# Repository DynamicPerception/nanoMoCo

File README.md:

nanoMoCo Stepper Controller/Driver
==================================

The nanoMoCo stepper driver/controller is a specialized, Arduino-compatible* device specifically designed to enable advanced multi-axis stepper-based robotics and automation projects less expensive, and easier to create.

This github contains the Eagle files, BOM, and Sketchup files for this board.  To purchase a pre-made board, see http://dynamicperception.com/products/nanomoco-stepper-drivercontroller

Key features of the nanoMoCo include:

- Atmega328P processor running at 16MHz
- 8-16V DC Operation
- Integrated A4983/A4988 bi-polar chopping driver with up to 16x microstepping
     - Up to 800 mA/coil without active cooling
     - Up to 1.5 A/coil with active cooling
- Dual opto-coupled outputs for safe interaction with other devices
- Integrated RS485 bus for multi-node communication over long distances with only two wires
- Leverage the OpenMoCo AVR Libraries and OpenMoCo Qt Libraries to create new software and applications

* requires a special USB to RS485 adapter to use with the Arduino IDE

See http://dynamicperception.com/docs/nanomoco for more information

License and Copyright
---------------------

nanoMoCo is Copyright (c) 2012-2013 Dynamic Perception LLC.

All files shared under the Creative Commons Attibution-Share-Alike 3.0 License.

The nanoMoCo name is a trademark of Dynamic Perception LLC.

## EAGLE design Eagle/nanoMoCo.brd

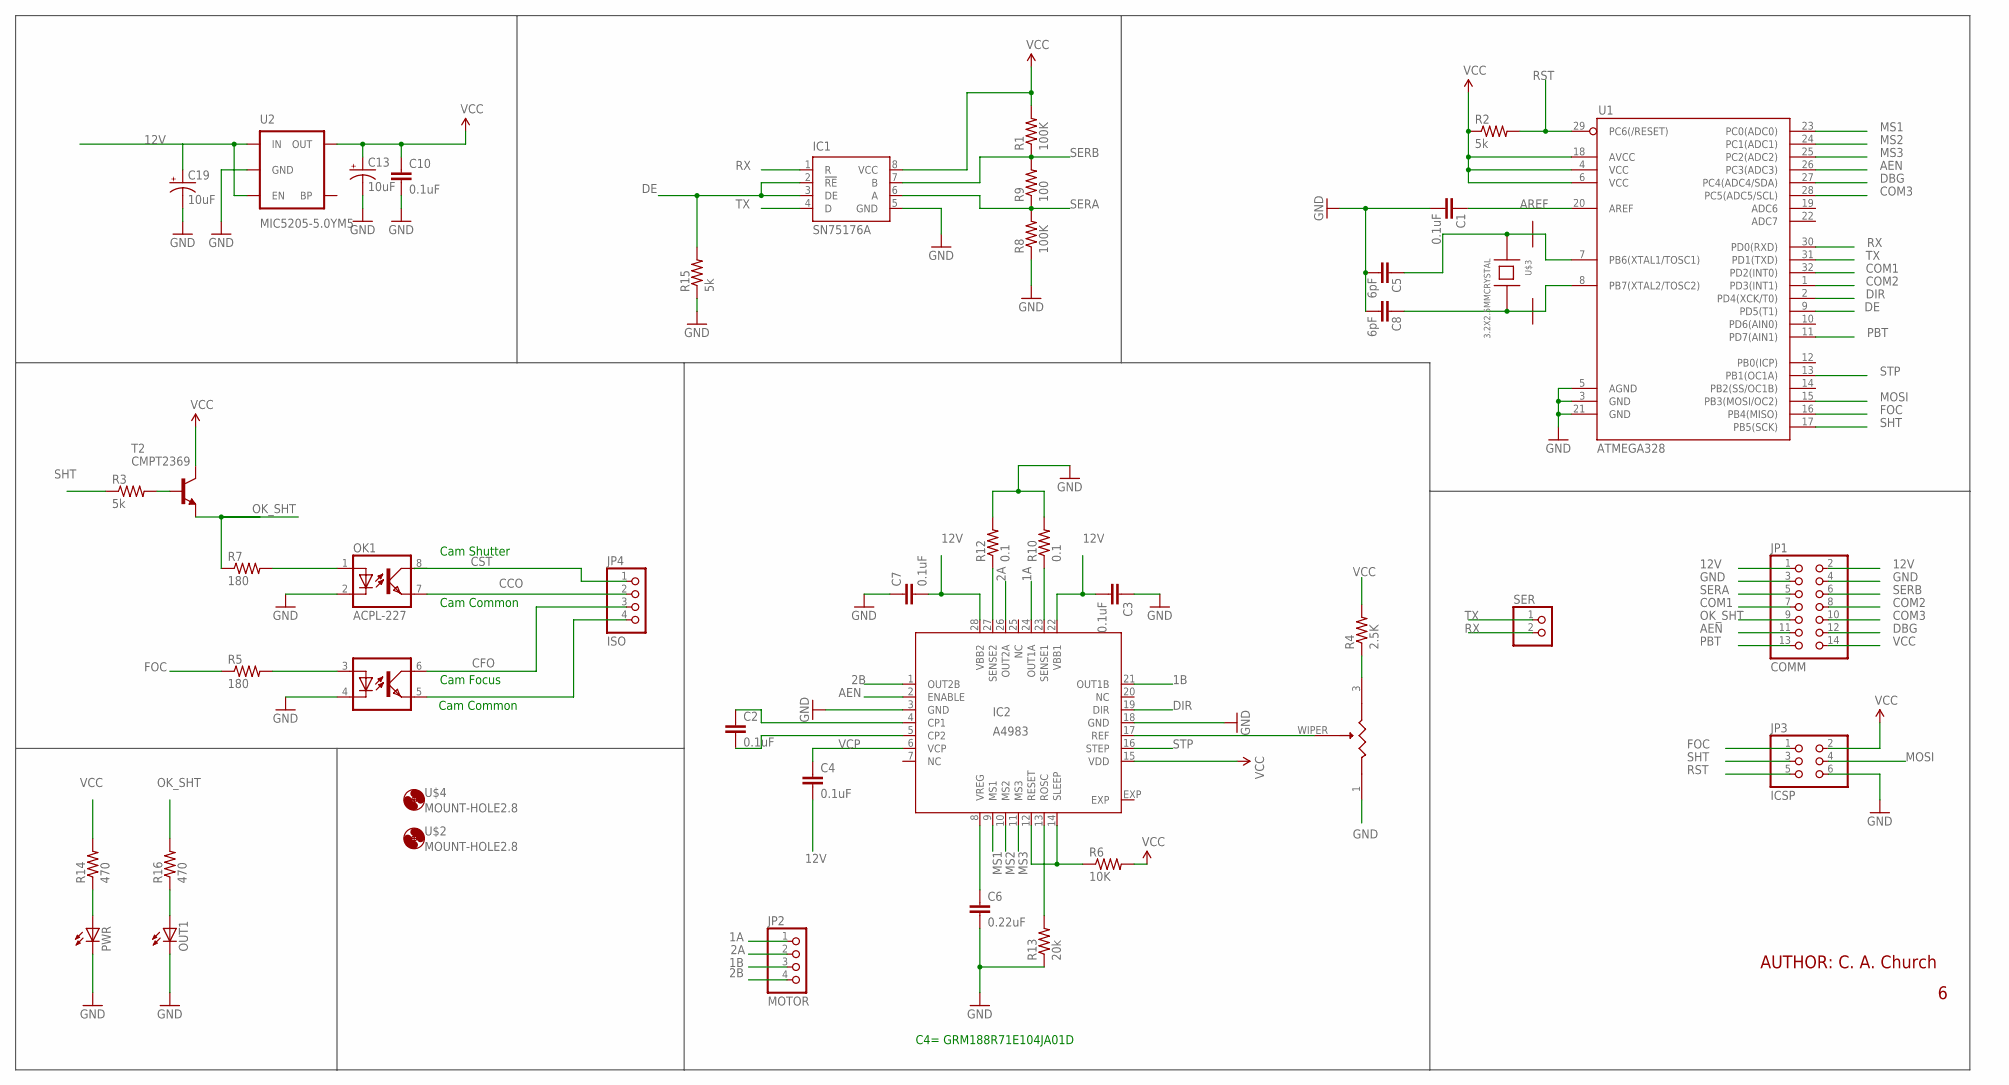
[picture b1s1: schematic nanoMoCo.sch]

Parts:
C1, C10: 0.1uF; C0402
C2, C3, C4, C7: 0.1uF; C1608
C5, C8: 6pF; C0402
C6: 0.22uF; C0805
C13, C19: 10uF; EIA3216
IC1: SN75176A; SO-08
IC2: A4983; QFN28ET
JP1: COMM; 2X07
JP2: MOTOR; 1X04
JP3: ICSP; 2X03
JP4: ISO; 1X04
OK1: ACPL-227; SOIC8
OUT1: LEDCHIPLED_0603; CHIPLED_0603
PWR: LEDCHIPLED_0603; CHIPLED_0603
R1, R8: 100K; C0402
R2, R3, R15: 5k; C0402
R4: 2.5K; C0402
R5, R7: 180; C0402
R6: 10K; C0402
R9: 100; C0402
R10, R12: 0.1; R0603
R13: 20k; C0402
R14, R16: 470; C0402
SER: PINHD-1X2; 1X02
T2: CMPT2369; SOT23-BEC
U1: ATMEGA328; TQFP32-08
U2: MIC5205-5.0YM5; SOT23-5
U$1: CADJ; 3MMSMD
U$2, U$4: MOUNT-HOLE2.8; 2,8
U$3: 3.2X2.5MMCRYSTAL; 3.2X2.5MM

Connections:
1A: IC2.24 (OUT1A), JP2.1
1B: IC2.21 (OUT1B), JP2.3
2A: IC2.26 (OUT2A), JP2.2
2B: IC2.1 (OUT2B), JP2.4
3.3V: IC1.8 (VCC), R1.2
4: U$3.4
12V: C3.2, C4.2, C7.2, C19.A (+), IC2.22 (VBB1), IC2.28 (VBB2), JP1.1, JP1.2, U2.1 (IN), U2.3 (EN)
AEN: IC2.2 (ENABLE), JP1.11, U1.26 (PC3(ADC3))
AREF: C1.2, U1.20 (AREF)
ARST: IC2.12 (RESET), IC2.14 (SLEEP), R6.1
CCO: JP4.2, OK1.7 (EMIT)
CFO: JP4.3, OK1.6 (COL1)
COM1: JP1.7, U1.32 (PD2(INT0))
COM2: JP1.8, U1.1 (PD3(INT1))
COM3: JP1.10, U1.28 (PC5(ADC5/SCL))
CST: JP4.1, OK1.8 (COL)
DBG: JP1.12, U1.27 (PC4(ADC4/SDA))
DE: IC1.2 (!RE), IC1.3 (DE), R15.2, U1.9 (PD5(T1))
DIR: IC2.19 (DIR), U1.2 (PD4(XCK/T0))
FOC: JP3.1, R5.1, U1.16 (PB4(MISO))
GND: C1.1, C3.1, C5.1, C6.2, C7.1, C8.1, C10.2, C13.C (-), C19.C (-), IC1.5 (GND), IC2.3 (GND), IC2.18 (GND), JP1.3, JP1.4, JP3.6, OK1.2 (C), OK1.4 (C1), OUT1.C, PWR.C, R8.1, R10.2, R12.2, R13.1, R15.1, U1.3 (GND), U1.5 (AGND), U1.21 (GND), U2.2 (GND), U$1.1, U$3.2 (GND)
MOSI: JP3.4, U1.15 (PB3(MOSI/OC2))
MS1: IC2.9 (MS1), U1.23 (PC0(ADC0))
MS2: IC2.10 (MS2), U1.24 (PC1(ADC1))
MS3: IC2.11 (MS3), U1.25 (PC2(ADC2))
unnamed: R4.1, U$1.3
unnamed: PWR.A, R14.1
unnamed: OUT1.A, R16.1
unnamed: C2.1, IC2.4 (CP1)
unnamed: C2.2, IC2.5 (CP2)
unnamed: JP4.4, OK1.5 (EMIT1)
unnamed: OK1.1 (A), R7.2
unnamed: OK1.3 (A1), R5.2
unnamed: IC2.17 (REF), U$1.WIPER (2)
unnamed: IC2.23 (SENSE1), R10.1
unnamed: IC2.27 (SENSE2), R12.1
unnamed: R3.2, T2.B
OK_SHT: JP1.9, R7.1, R16.2, T2.E
PBT: JP1.13, U1.11 (PD7(AIN1))
ROSC: IC2.13 (ROSC), R13.2
RST: JP3.5, R2.2, U1.29 (PC6(/RESET))
RX: IC1.1 (R), SER.2, U1.30 (PD0(RXD))
SERA: IC1.6 (A), JP1.5, R8.2, R9.1
SERB: IC1.7 (B), JP1.6, R1.1, R9.2
SHT: JP3.3, R3.1, U1.17 (PB5(SCK))
STP: IC2.16 (STEP), U1.13 (PB1(OC1A))
TX: IC1.4 (D), SER.1, U1.31 (PD1(TXD))
VCC: C10.1, C13.A (+), IC2.15 (VDD), JP1.14, JP3.2, R2.1, R4.2, R6.2, R14.2, T2.C, U1.4 (VCC), U1.6 (VCC), U1.18 (AVCC), U2.5 (OUT)
VCP: C4.1, IC2.6 (VCP)
VREG: C6.1, IC2.8 (VREG)
XTAL1: C5.2, U1.7 (PB6(XTAL1/TOSC1)), U$3.1
XTAL2: C8.2, U1.8 (PB7(XTAL2/TOSC2)), U$3.3

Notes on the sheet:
Cam Shutter
Cam Common
Cam Focus
C4= GRM188R71E104JA01D
AUTHOR: C. A. Church

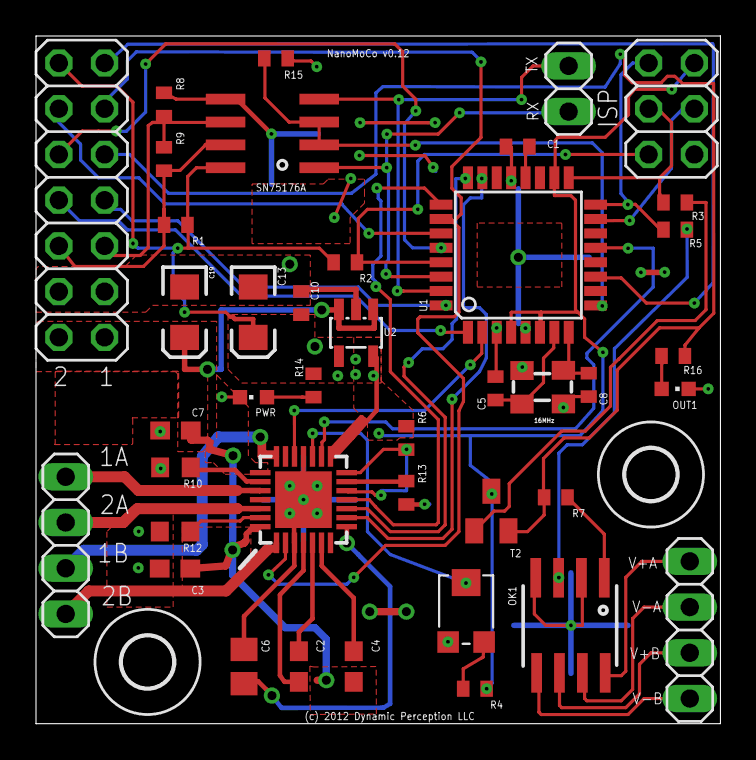
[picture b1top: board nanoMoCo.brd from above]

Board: 2 copper layers, 38.0 x 38.2 mm, 43 parts (0 on the bottom side), 51 nets.

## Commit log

2013-03-27 * Added required files
2013-03-27 * Added License file
2013-03-28 * Added Schematic PDF
2013-03-28 * Added text to README

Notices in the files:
Eagle/nanoMoCo.brd:
(c) 2012 Dynamic Perception LLC
